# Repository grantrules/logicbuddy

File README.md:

# LogicBuddy

A durable, easy-to-solder printed circuit board featuring clear diagrams and labels for each component. Gain practical experience with soldering and circuit assembly, boosting your confidence and skillset! Discover how logic gates serve as the backbone of modern electronics, from simple devices to complex computers, and assemble a NAND latch to understand memory storage in digital circuits.

# Parts

| Reference | Value |
| --- | --- |
| D1-D4 | LED |
| Q1-Q7 | NPN Transistor |
| R1-R4 | 345Ω resistor |
| R5-R11 | 1kΩ resistor |
| R12-13 | 10kΩ resistor |
| SW1-7 | SPST Switch |
| SW8 | DIP Switch |

## Gates

* [AND Gate](https://www.falstad.com/circuit/circuitjs.html?ctz=CQAgjCAMB0l3BWcMBMcUHYMGZIA4UA2ATmIxAUgpABZsKBTAWjDACgA3W7FcY3urzA0aUMTSpIq06AjYAXECjx5wYXtmyE1vKhBgISdCXgyEMkFAhTEo0QggwoaYYpBoYaxBGFVg4IAAmDABmAIYArgA28gpKKuBmIJraYEl6doZkGMTY1jQIZG6qMA54WuZg2MQE+DnIVMHh0bEAzkr4Sk5dvJi6YuFRrQxs7cqqfcnWPWJUg8NsAE4dExIzztIgbnBL8atUeb1rVNuQbIHJeKKEoikgN0pBoZExTFEMgbvYV-eigr9iXBnADuSmcOj2EJByS0ALuxG00Lu6lUyMI0jYoOR-G4Qhx0JQ4NYvU6GygmPW3UmZIJCTQEwSaURFP+40hbNpDK5M057NJCQJ-ImpO6vLJbPp5Kx0zJhx5LJ4kJoDw5LJVCWVomEomhmvAIlx+p1Ct4D3+2vJQA)
* [OR Gate](https://www.falstad.com/circuit/circuitjs.html?ctz=CQAgjCAMB0l3BWcMBMcUHYMGZIA4UA2ATmIxAUgpABZsKBTAWjDACgA3W7FcY3urzA0aUMTSpIq06AjYAXECjx5wYXtmyE1vKhCY1ZNPBmU1CNBCTB5RqGxIvFbx9WCRg4IACYMAZgCGAK4ANvIKSirgGNqa2mAxYvqGCMamthYIxJAJ2va2kE62mOqkQl6+gaHhAM5K+EqmjbyYuuAggSE1DGx1yqqtINgILU16HQFdPQBO9QMSzUoLVNlwbLP9S1TDLcsgq5Bs3kO2IBZDWmeivJXBYUwhDN7rJ6LngldiuIcA7kooolYLSiQKgbD+cU+kOIeXBF3i-CGhFUYERv3+gPUcy2YL+g3xTQB0jhH02ZKi6PJAyig0pNJpDU2lMZDIGYzhZIWZIa6J2OL5tJJPEiqnM1wpJPOmzF4BEuNo52Eog+SvlH3ewtVvMu6lUWhRynl+r4GmR4ENvLNqIEmrRcOhsVOMKNTsdgMIxIhpzAHvh4F9dIGLJRiUOQA)
* [NOT Gate](https://www.falstad.com/circuit/circuitjs.html?ctz=CQAgjCAMB0l3BWcMBMcUHYMGZIA4UA2ATmIxAUgpABZsKBTAWjDACgA3WmvEFGqjR7hiKKOIHUq06AjYAXPhjFhCVbAhVrxEFrOJ4ENDHmIIyxbMQgwwojRkJgTKFKQSFeYOCAAmDADMAQwBXABt5NgBnEA0xbDRuXgTpcBBgsKiGNgAnJXjEuNjEqm84Nl9YzXAhWlUamj4-QNCIpjCGX1yqlVqiwkb1coB3OsIGsb5JSDZRmnr+QWFFqFmekAGkjcG1oV5NvZExGdGi53GilA9V0+qr8cP7m62Vx+uTrbsxHlLRZ5+jrQ8OoSrtgcUlslQaNMAUqLDwNoZkA)
* [NAND latch](http://www.falstad.com/circuit/circuitjs.html?ctz=CQAgjCAMB0l3BWcMBMcUHYMGZIA4UA2ATmIxAUgpABZsKBTAWjDACgA3WmvEQm7rxaEoomlSRUp0BGwDuIbNhHiqNYirhQ2AF3AYRYESnHgRVCExrRsxbBgR5CkDGXV0osHNjyuENQjwfNAwBMC0AEwYAMwBDAFcAGx1dfREmfhATKgyBC08EQiKaGgQwPBoDSCNyGH44bBMUIOJIFGIPcKoouKSUgCdFSAEmPCpsBBQQUalkODZB1imjNLNRLsgF8DAp3NW9i3g2AGdt3cyeacz8uMTjhhOztcuVm9i7h4VlISXFNGnfpsvv8WDtaD8wUDwQCwZcDvJoXsXuYEdk-llTICtr8xqtXnN5osDFcBGjZhtNoMSj8RD4RviJpsIooKgDaf8qFMeglkgicZyMFNcVDMEKBbthajTFZeM0hJcRXh5bKlejFbxGhjxlMoY1ZmTtAo0b9qU8oaaLi9IVKcrjRdNJUbBQ7xsMXYbFJN3d93brAjCpj6Zh6g7jTcHzXCw3DXmwgA)

[Parts list](https://docs.google.com/spreadsheets/d/e/2PACX-1vQcbd3u2FSdjSrrMugmj8Pl3sIFiQrY80xA-rvQpsKqJZOuXIbTLq43Xqpactsh0kT7ian0Zf0PcqA9/pubhtml)

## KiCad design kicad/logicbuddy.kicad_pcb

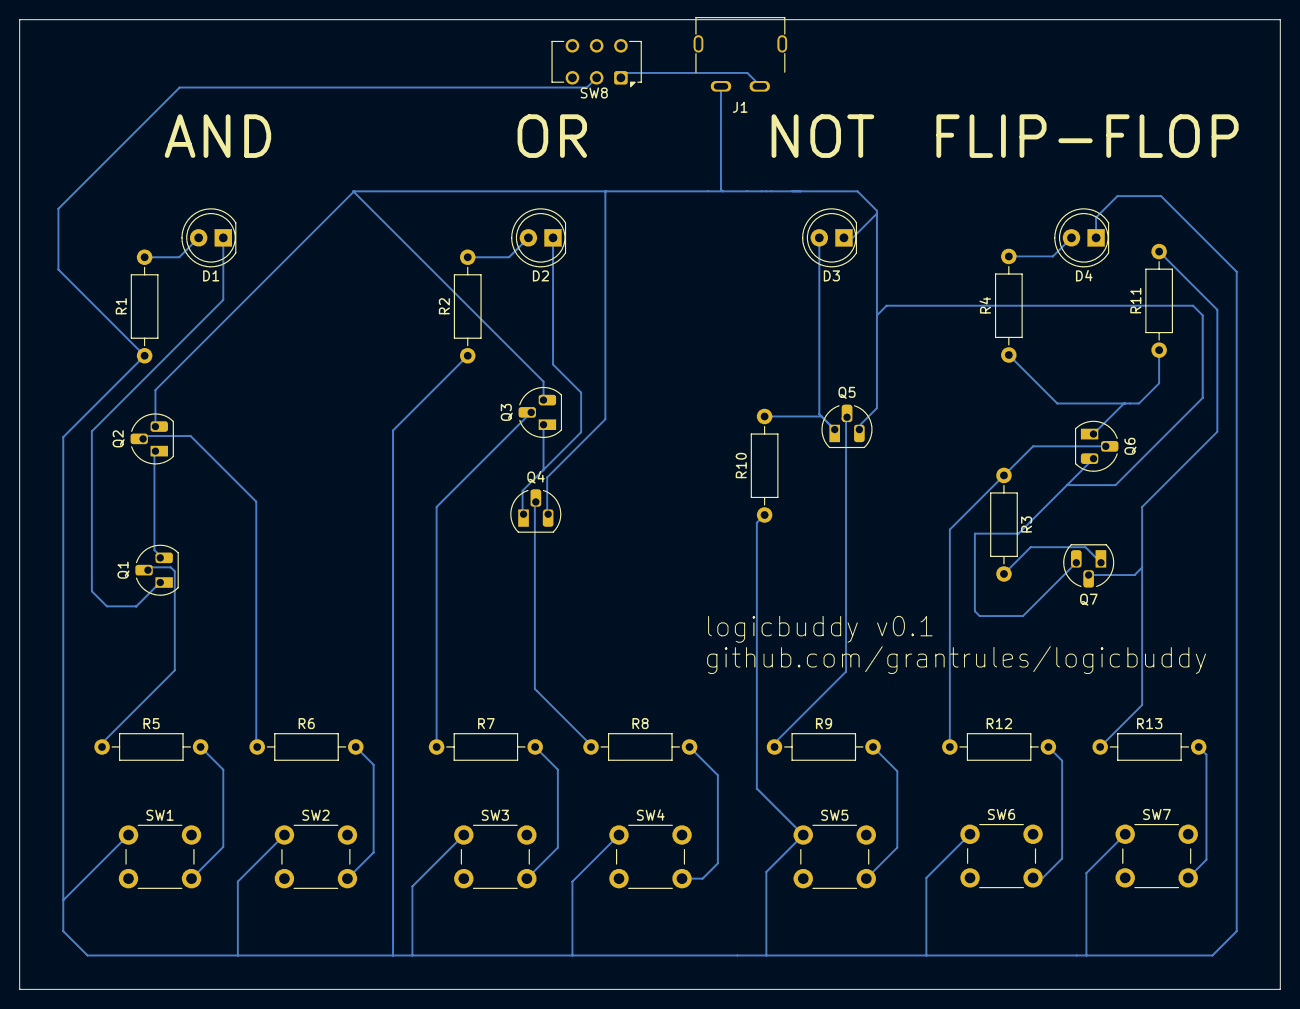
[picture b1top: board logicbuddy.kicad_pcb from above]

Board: 2 copper layers, 130.0 x 100.0 mm, 33 parts (0 on the bottom side), 26 nets.

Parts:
D1, D2, D3, D4: LED; LED_D5.0mm
J1: USB_C_2PIN; USB_C_2pin-aliexpress
Q1, Q2, Q3, Q4, Q5, Q6, Q7: NPN; TO-92L_HandSolder
R1, R2, R4, R10: 345; R_Axial_DIN0207_L6.3mm_D2.5mm_P10.16mm_Horizontal
R3, R11: 10k; R_Axial_DIN0207_L6.3mm_D2.5mm_P10.16mm_Horizontal
R5, R6, R7, R8, R9, R12, R13: 1k; R_Axial_DIN0207_L6.3mm_D2.5mm_P10.16mm_Horizontal
SW1, SW2, SW3, SW4, SW5, SW6, SW7: SW_SPST; SW_PUSH_6mm_H5mm
SW8: SW_DIP_x01; SW_CK_JS202011CQN_DPDT_Straight

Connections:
unnamed: D1.2 (A), R1.2
unnamed: D1.1 (K), Q1.1 (C)
unnamed: D2.2 (A), R2.2
unnamed: D2.1 (K), Q3.1 (C), Q4.1 (C)
unnamed: D3.2 (A), Q5.1 (C), R10.2
unnamed: D3.1 (K), J1.A1 (GND), Q2.3 (E), Q3.3 (E), Q4.3 (E), Q5.3 (E), Q6.3 (E), Q7.3 (E)
unnamed: D4.2 (A), R4.2
unnamed: D4.1 (K), R1.1, R2.1, R10.1, SW1.1 (A), SW2.1 (A), SW3.1 (A), SW4.1 (A), SW5.1 (A), SW6.1 (A), SW7.1 (A), SW8.2
unnamed: J1.A4 (VBUS), SW8.1
unnamed: Q1.2 (B), R5.1
unnamed: Q1.3 (E), Q2.1 (C)
unnamed: Q2.2 (B), R6.1
unnamed: Q3.2 (B), R7.1
unnamed: Q4.2 (B), R8.1
unnamed: Q5.2 (B), R9.1
unnamed: Q6.2 (B), R3.1, R12.1
unnamed: Q6.1 (C), R4.1, R11.1
unnamed: Q7.2 (B), R11.2, R13.1
unnamed: Q7.1 (C), R3.2
unnamed: R5.2, SW1.2 (B)
unnamed: R6.2, SW2.2 (B)
unnamed: R7.2, SW3.2 (B)
unnamed: R8.2, SW4.2 (B)
unnamed: R9.2, SW5.2 (B)
unnamed: R12.2, SW6.2 (B)
unnamed: R13.2, SW7.2 (B)

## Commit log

2024-09-17 add not gate sim
2024-09-17 cleaned up not
2024-09-17 cleaned up and sim
2024-09-17 add or gate sim
2024-09-17 pcb cleanup
2024-10-05 fixed names and values
2024-11-10 fix pcb
2024-11-13 fixed usb port, added versioning
2024-11-13 rename to logicbuddy
2024-11-13 metadata update
2024-11-30 add .lck to gitignore
2024-11-30 updated labels and fixed footprints
2024-11-30 Revert "updated labels and fixed footprints"
    This reverts commit cc8675b157493e85bb3edc9923989f4c8e1865eb.
2024-11-30 Reapply "updated labels and fixed footprints"
    This reverts commit 2a946a7896d612220efc5a586cb72ca7f3163489.
2024-11-30 fix labels and footprints
2025-06-10 add image
